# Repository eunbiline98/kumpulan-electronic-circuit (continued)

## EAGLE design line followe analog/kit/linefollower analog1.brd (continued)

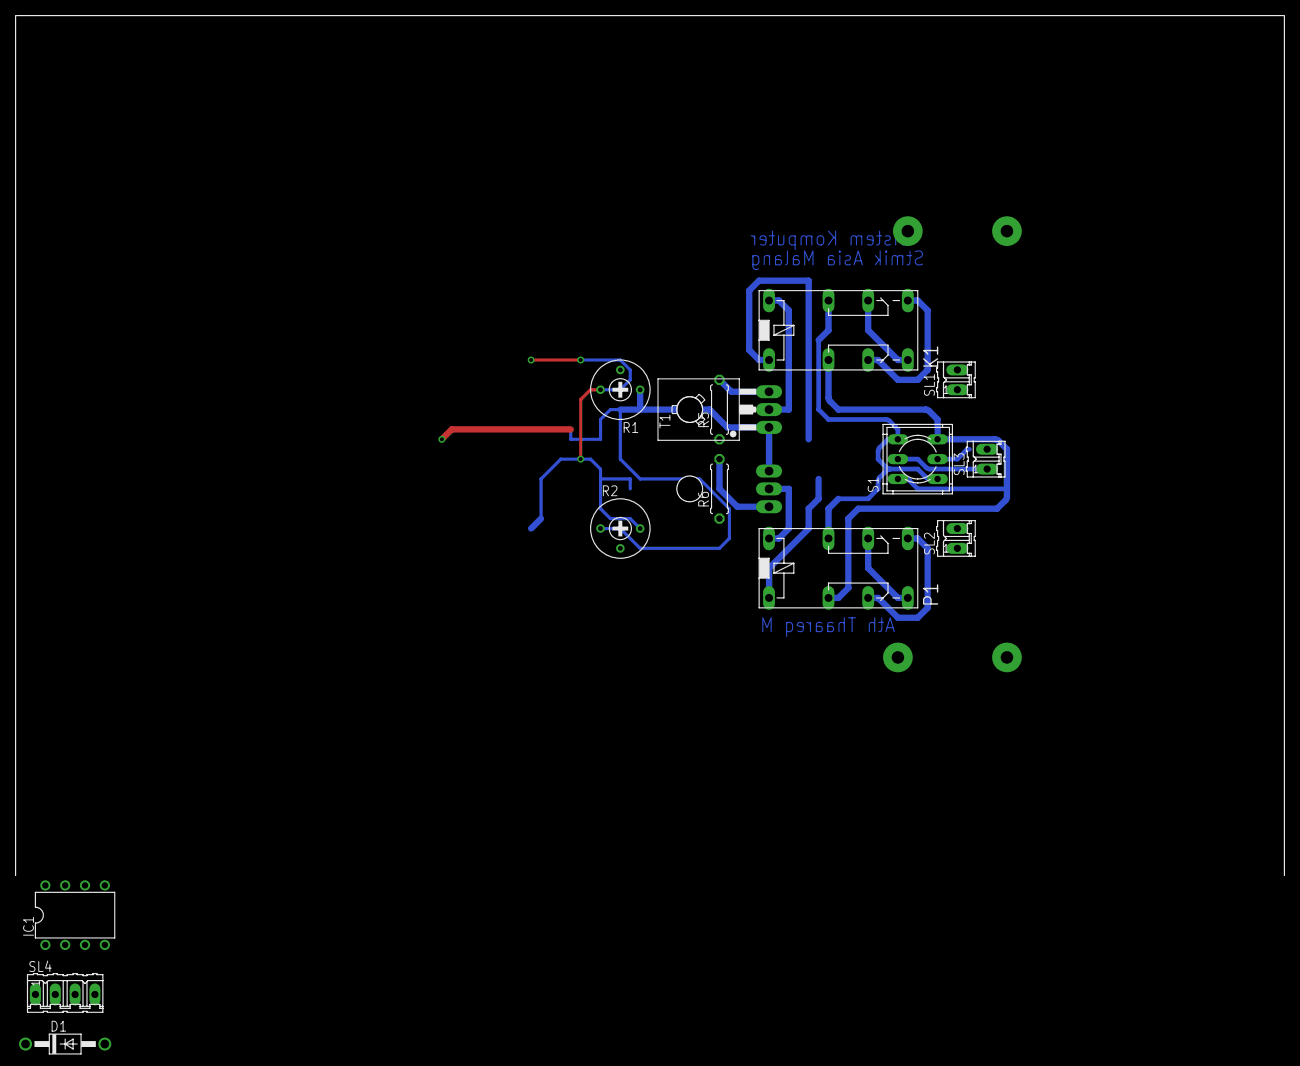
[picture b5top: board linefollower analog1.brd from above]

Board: 2 copper layers, 162.5 x 110.2 mm, 15 parts (1 on the bottom side), 21 nets.

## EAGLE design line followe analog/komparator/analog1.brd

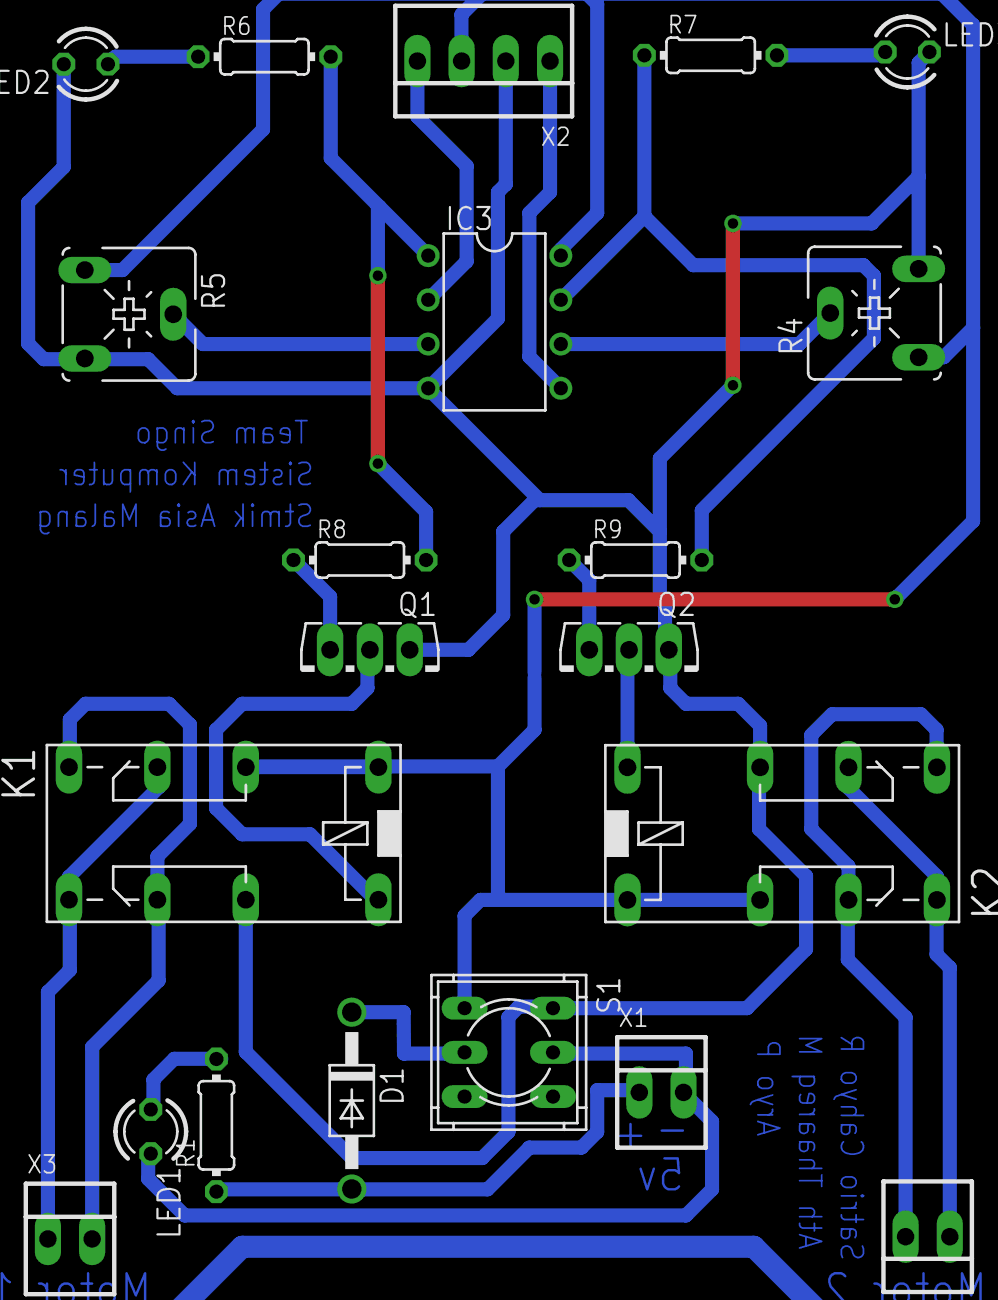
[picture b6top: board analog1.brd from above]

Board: 2 copper layers, 21 parts (0 on the bottom side), 21 nets.

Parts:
D1: 1N4004; DO41-10
IC3: LM358N; DIL08
K1, K2: 351
LED1, LED2, LED3: LED3MM
Q1, Q2: BD139; TO126AV
R1, R6, R7, R8, R9: 0204/7
R4, R5: CA6V
S1: 9077-2
X1, X3, X4: 22-23-2021
X2: 22-23-2041

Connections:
GNDA: IC3.4, K1.P2, K2.P2, LED2.K, LED3.K, Q1.E, Q2.E, R4.E, R5.E, S1.1, X2.2
unnamed: D1.C, S1.5
unnamed: K2.O1, K2.S2, X4.2
unnamed: IC3.2, X2.4
unnamed: IC3.5, X2.1
unnamed: IC3.3, R5.S
unnamed: IC3.6, R4.S
unnamed: IC3.1, R6.2, R8.2
unnamed: LED2.A, R6.1
unnamed: LED3.A, R7.2
unnamed: IC3.7, R7.1, R9.2
unnamed: Q2.B, R9.1
unnamed: Q1.B, R8.1
unnamed: K1.16, Q1.C
unnamed: K2.16, Q2.C
unnamed: K2.O2, K2.S1, X4.1
unnamed: K1.O2, K1.S1, X3.2
unnamed: K1.O1, K1.S2, X3.1
S$7: K1.1, K1.P1
S$8: K2.1, K2.P1, S1.4
VCC: IC3.8, R4.A, R5.A, X2.3

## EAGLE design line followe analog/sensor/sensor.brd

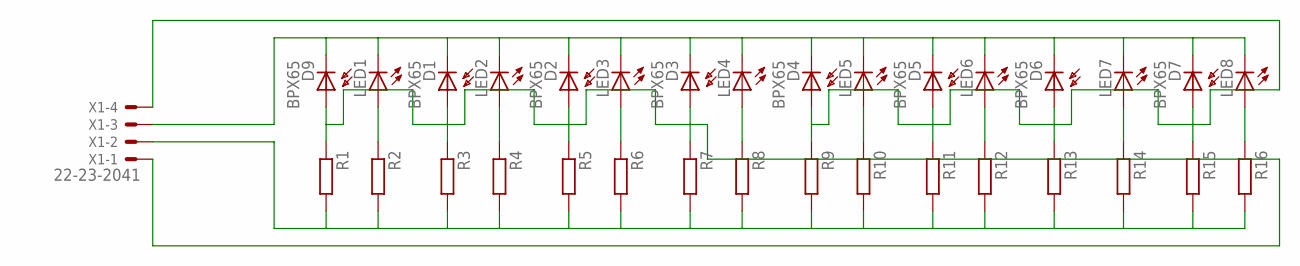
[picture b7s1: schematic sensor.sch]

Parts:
D1, D2, D3, D4, D5, D6, D7: BPX65; MPN BPX65.
D9: BPX65
LED1, LED2, LED3, LED4, LED5, LED6, LED7, LED8: LED3MM
R1, R2, R3, R4, R5, R6, R7, R8, R9, R10, R11, R12, R13, R14, R15, R16: R-EU_0204/7; 0204/7
X1: 22-23-2041

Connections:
unnamed: D1.A, D2.A, D3.A, D9.A, R1.1, R3.1, R5.1, R7.1, X1.1
unnamed: LED1.A, R2.1
unnamed: LED2.A, R4.1
unnamed: LED3.A, R6.1
unnamed: LED4.A, R8.1
unnamed: D4.A, D5.A, D6.A, D7.A, R9.1, R11.1, R13.1, R15.1, X1.4
unnamed: LED5.A, R10.1
unnamed: LED6.A, R12.1
unnamed: LED7.A, R14.1
unnamed: LED8.A, R16.1
unnamed: D1.K (C), D2.K (C), D3.K (C), D4.K (C), D5.K (C), D6.K (C), D7.K (C), D9.K (C), LED1.K (C), LED2.K (C), LED3.K (C), LED4.K (C), LED5.K (C), LED6.K (C), LED7.K (C), LED8.K (C), X1.3
unnamed: R1.2, R2.2, R3.2, R4.2, R5.2, R6.2, R7.2, R8.2, R9.2, R10.2, R11.2, R12.2, R13.2, R14.2, R15.2, R16.2, X1.2

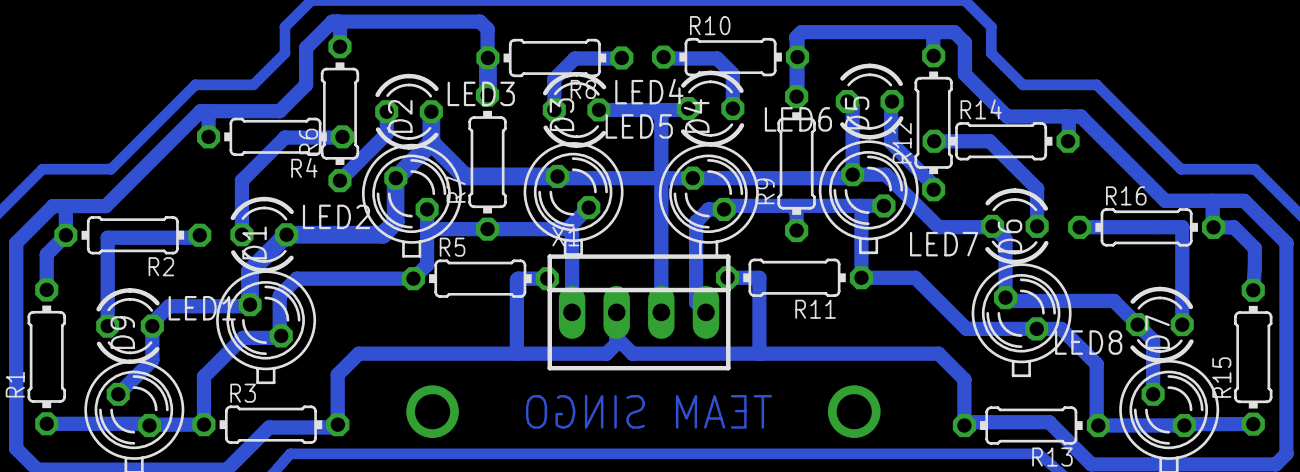
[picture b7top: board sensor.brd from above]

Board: 2 copper layers, 33 parts (0 on the bottom side), 12 nets.
